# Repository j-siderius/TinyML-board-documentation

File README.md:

# TinyML Board Documentation

The TinyML board is a development board specifically tailored to the exploration of TinyML concepts and to test possible applications of TinyML in an easy way. It features a powerfull microcontroller as well as a suite of sensors to sense the environment. Combined with a special TensorFlow Lite Micro library, it is easy to use this devide and start deploying machine learning models to the Edge.

<div align="center">
    
</div>

## Contents
- [Quick start](#quick-start)
- [Hardware](#hardware)
  - [Sensors](#sensors)
  - [Processor](#processor)
  - [Input/Output](#inputoutput)
  - [Expansion headers](#expansion-headers)
- [Software](#software)
  - [Arduino](#arduino-ide)
  - [IDE configuration](#ide-configuration)
  - [Serial Port Setup](#serial-port-setup)
  - [Libraries](#arduino-libraries)
  - [TensorFlow Lite Micro library](#tensorflow-lite-micro-library)
  - [Uploading code](#uploading-code)
- [Code examples](#code-examples)
  - [Sensor examples](#sensor-examples)
  - [I/O examples](#io-examples)
  - [TensorFlow Lite Micro examples](#tensorflow-lite-micro-examples)
  - [Board tests](#board-tests)
- [Frequently Encountered Issues](#frequently-encountered-issues)
- [License](#license-and-contact)

## Quick start

 1. Install the ESP32 board support into Arduino IDE by adding the Espressif repository to the Board Manager and then downloading the ESP32 boards - [Espressif Arduino ESP32 installation](https://docs.espressif.com/projects/arduino-esp32/en/latest/installing.html#installing-using-arduino-ide).
 2. Install libraries for the sensors ([Sparkfun BME280](https://github.com/sparkfun/SparkFun_BME280_Arduino_Library), [Sparkfun BMI270](https://github.com/sparkfun/SparkFun_BMI270_Arduino_Library), [Pololu VL53L0X](https://github.com/pololu/vl53l0x-arduino) and [FastLED](https://github.com/FastLED/FastLED)) using the Library Manager and TensorFlow Lite Micro ([TFLiteMicro_ArduinoESP32S3](https://github.com/j-siderius/TFLiteMicro_ArduinoESP32S3)) from the GitHub page.
 3. Choose an [example project](#code-examples) for the TinyML board and load the code into Arduino IDE.
 4. Configure the TinyML board using the [Arduino IDE settings](#ide-configuration). Press and hold the `Upload/Btn1` button, then press the `RESET` button. Release all buttons and click `Upload`, then wait for the code to upload.
 5. Check the Serial Monitor or Serial Plotter in Arduino IDE to see the output from the model.

More detailed instructions can be found in the corresponding sections below.

[🔼 Back to the top](#tinyml-board-documentation)

## Hardware

The TinyML board contains several sensors and a powerfull processor to get up and running with TinyML quickly. In the following sections, a general overview as well as technical details on all hardware can be found.

<div align="center">
    
</div>

### Sensors

The TinyML board contains five different sensors that can be used for gathering data. To see how to use the sensors, look at the [Code Examples](#code-examples). For detailed information about the circuit board, refer to the [Circuit board documentation](/pcb/README.md).

- **Microphone (I2S)** [_ICS-43434_](assets/datasheets/ics43434.pdf) - This sensor measures the amplitude and pitch of sound.
- **Time-of-Flight range sensor** [_VL53L0X_](assets/datasheets/vl53l0x.pdf) - This sensor measures short-range distance.
- **Environmental sensor** [_BME280_](assets/datasheets/bme280.pdf) - This sensor measures temperature, relative humidity and atmospheric pressure.
- **Hall effect magnet sensor** [_AH49E_](assets/datasheets/ah49e.pdf) - This sensor measures the magnetic field around its axis.
- **Inertial Measurement Unit (IMU)** [_BMI270_](assets/datasheets/bmi270.pdf) - This sensor measures both the angular motion using a gyroscope, as well as the acceleration using an accelerometer.

### Processor

The TinyML board is fitted with an ESP32-S3 SoC. The processor features a fast 240MHz, dual-core processor, large 16MB storage and 8MB RAM. 
Additionally, it has Bluetooth 5 and WiFi capabilities, making it easy to connect the TinyML board to the internet, for example to share sensor data.
More information about the onboard chip can be found in the datasheet: [ESP-S3-WROOM1-N16R8](assets/datasheets/esp32s3wroom1.pdf).

### Input/Output

Besides sensors, the TinyML board also contains multiple Inputs and Outputs (I/O). To see how to use the I/O, look at the [Code Examples](#code-examples).

- **Buttons** - Two buttons are accessible to the user (`Upload/Btn1` and `Btn2`), which can be user-configured. Both buttons need to be pulled high by the processor (see the [Code Examples](#code-examples)).
  The last button (`RESET`) is used if the board needs to be programmed or debugged, e.g. if the TinyML board or the application need to be restarted.
- **Output LED** - The red LED can be used as simple output, e.g. for showing if a sensor functions properly. The output LED is marked `LED` on the TinyML board.
- **Neopixels** - The Neopixel LEDs can be addressed individually to display RGB colors. They can output application information, give users feedback and more. The Neopixels are marked `Neopixels` on the TinyML board.

- **USB-C connector** - This connector is primarily used for programming and serial communication with the TinyML board. It is also the primary power input for the board. To program the board, a USB-C _Data_ cable is needed.
- **Stemma QT / QWIIC** - This connector enables users to connect extra sensors, making the TinyML board suitable for even more advanced projects.
  The connector uses the popular [Adafruit Stemma QT](https://www.adafruit.com/category/620) and [SparkFun QWIIC](https://www.sparkfun.com/categories/399) standards, opening up the possibilty for many extra sensors.
  Using a Stemma QT expansion board, users can connect even more sensors in series. For the pinout, refer to the [Expansion headers](#expansion-headers) section. This connector if marked `Stemma QT/QWIIC` on the TinyML board.
- **Expansion header** - This connector can be used to connect extra peripherals, sensors, actuators and more to adapt the TinyML board to different projects. This connector is marked `Expansion Header` on the TinyML board.
  The connector features power, digital and analog connections, as well as support for the SPI high-speed databus. In combination with the ESP32S3's built in GPIO multiplexer, the connector gives the freedom to connect many different things to the TinyML board.
  For the pinout, refer to the [Expansion headers](#expansion-headers) section.

- **Miscellaneous** - The TinyML board also contains some other, miscellaneous component.
  These components are used to show power (green LED, marked `ON` on the TinyML board), convert voltage, debug the TinyML board (header, marked `Debugging` on the TinyML board) and some other passive components. Additionally, the board features some test-points (2x GND, VUSB, 3.3V and IO0) which can be used to verify the functionality of some components.

### Expansion headers

Below a systematic overview of all expansion headers present on the TinyML board is shown. The Expansion header features four analog GPIO pins (A1 - A4 in the top row), four digital GPIO pins (D1 - D4 in the bottom row), as well as 3.3V power and ground (GND). The digital GPIO pins also expose the SPI data bus of the ESP32S3 microcontroller as follows:

| GPIO pin | Description |
| --- | --- |
| D1 / GPIO14 | SPI CS |
| D2 / GPIO11 | SPI MOSI |
| D3 / GPIO12 | SPI SCK |
| D4 / GPIO13 | SPI MISO |

The TinyML board can technically be powered through the Expansion Header, but the power should be stable and noise-free **3.3V** only. If the external power is fluctuating, the microcontroller could be damaged. If it is absolutely nescessary to provide variable external power from another source than USB-C (e.g. from a battery), it is possible to utilise the testpoints GND and VUSB close to the USB-C connector on the board. The VUSB testpoint routes the power through the on-board voltage regulator first, which produces clean 3.3V.

<div align="center">
    
</div></div>

[🔼 Back to the top](#tinyml-board-documentation)

## Software

In order to use the TinyML board, it needs to be correctly setup. The TinyML board requires no hardware setup, but it does require some software setup. In order to start using it, connect a USB-C _Data_ cable to the board and plug it into a free USB port on the system. Below sections detail the setup of the Arduino IDE, installation of sensor libraries and finally the TensorFlow Lite Micro setup.

### Arduino IDE

The TinyML board can be programmed using the [Arduino IDE](https://www.arduino.cc/en/software), both the new 2.x and Legacy >1.8 versions.
Please make sure that the Arduino IDE is installed on the system before continuing.

In order to program the TinyML board, the [ESP32](#processor) platform need to be installed. To do this, follow the steps below:

1. Open the Arduino IDE and navigate to the `Preferences` (_Windows_: File > Preferences, _Mac_: Arduino > Preferences), as shown in the left image below.
2. In the field `Additional boards manager URLs:` enter the following link (If there are already other URLs in this field,
   open the full list by clicking the folder icon to the right of the URL):
   ```
   https://espressif.github.io/arduino-esp32/package_esp32_index.json
   ```   
3. Press `Ok` to close the `Preferences`.
4. Open the `Boards Manager` by going to Tools > Boards > Boards Manager.
5. Search for **ESP32** and install the platform by Espressif Systems.
6. Restart the Arduino IDE.

<div align="center">

</div>

For more advanced installations, for example in Platform IO, follow this [advanced installation guide](https://docs.espressif.com/projects/arduino-esp32/en/latest/installing.html).

### IDE configuration

In order to use all functions that the ESP32S3 processor has, Arduino IDE must be properly configured when programming the TinyML board. Below are the most important settings, these need to be configured in the `Tools menu` (_Windows_ + _Mac_: Tools) by clicking on the setting and choosing the correct option:

- **Board** - *ESP32S3 Dev Module*: This sets the correct processor and board configuration for the TinyML board. To select the ESP32 Dev Module, first select the *esp* platform.
- **Port** - *port here*: Enter the serial port of the TinyML board here. Refer to the guide [Serial Port](#serial-port-setup) to find this port.
- **USB CDC On Boot** - *Enabled*: This setting enables the onboard USB-C port to be used for serial communication.
- **Flash mode** - *DIO 80MHz*: This setting configures the correct mode for writing to the flash of the ESP32S3.
- **Flash Size** - *16MB (128Mb)*: This setting uses the full storage of the ESP32S3, enabling space for larger projects and more code.
- **PSRAM** - *OPI PSRAM*: This setting enables the fast built-in RAM of the ESP32S3.

<div align="center">
    
</div>

### Serial Port setup

No drivers are required for the TinyML board. However, sometimes, it is nescessary to know on which serial port the TinyML board is connected. To find this out, perform the following steps:

_Arduino IDE_
1. Open the `Port overview menu` (_Windows_ + _Mac_: Tools > Port) and observe which ports are in the list. 
2. Close the list.
3. Plug in the TinyML board and open the `Port overview menu`, observe which port was added to the list > this is the TinyML board port.

If the above method does not work, an OS-specific check can be done using the instructions below:

_Windows_
1. Open `Device Manager` by going to Start and searching for the program. (Alternatively, press the <kbd></kbd> key and search for Device Manager)
2. Open the `Ports (COM & LPT)` section.
3. Plug in the TinyML board and observe which COM port was added to this list > this is the TinyML board port.

_Mac_
1. Open the `Terminal` application by going to Applications > Utilities. (Alternatively, press the <kbd> + Spacebar</kbd> keys and search for Terminal)
2. Enter the following command `ls /dev/tty*` and press <kbd>Enter</kbd>.
3. Plug in the TinyML board and repeat step 2, observe which port was added to the list > this is the TinyML board port.

### Arduino libraries

In order to use the sensors on the TinyML board, some Arduino libraries are needed. The recommended libraries are listed below, although other libraries might work as well.

The libraries can be installed into Arduino IDE through the Library Manager (Sketch > Include Library > Manage Libraries). The versions are included here for documentation purpose, the newest version of each library should work fine.

- [Sparkfun BME280](https://github.com/sparkfun/SparkFun_BME280_Arduino_Library) (2.0.10 or later)
- [SparkFun BMI270](https://github.com/sparkfun/SparkFun_BMI270_Arduino_Library) (1.0.3 or later)
- [Pololu VL53L0X](https://github.com/pololu/vl53l0x-arduino) (1.3.1 or later)
- [FastLED](https://github.com/FastLED/FastLED) (3.9.13 or later)

The onboard [Microphone](#sensors) uses the built-in I2S library from Espressif, so there is no library to install to use the microphone. More information can be found in the [I2S Peripherals documentation](https://docs.espressif.com/projects/esp-idf/en/v3.3/api-reference/peripherals/i2s.html). 

### TensorFlow Lite Micro library

In order to run TensorFlow Lite Micro models on the TinyML board, the [TFLiteMicro_ArduinoESP32S3](https://github.com/j-siderius/TFLiteMicro_ArduinoESP32S3) library needs to be installed. Download the libary from its homepage and install it in the Arduino IDE by using the Library Manager (Sketch > Include Library > Add .ZIP Library). More information on installing ZIP-libraries on Arduino can be found on the [Arduino website](https://docs.arduino.cc/software/ide-v1/tutorials/installing-libraries/#importing-a-zip-library).

> [!IMPORTANT]
> Be aware that not all TensorFlow (Keras) layers are supported by TensorFlow Lite Micro. Some layers may also have a different name in TensorFlow Lite Micro, compared to their name in TensorFlow (Keras), for example the `LSTM` layer is called `UnidirectionalSequenceLSTM`.
> 
> <details><summary>Supported layers</summary>
> Abs
> Add
> AddN
> ArgMax
> ArgMin
> AssignVariable
> AveragePool2D
> BatchMatMul
> BatchToSpaceNd
> BroadcastArgs
> BroadcastTo
> CallOnce
> Cast
> Ceil
> CircularBuffer
> Concatenation
> Conv2D
> Cos
> CumSum
> Delay
> DepthToSpace
> DepthwiseConv2D
> Dequantize
> DetectionPostprocess
> Div
> EmbeddingLookup
> Energy
> Elu
> Equal
> EthosU
> Exp
> ExpandDims
> FftAutoScale
> Fill
> FilterBank
> FilterBankLog
> FilterBankSquareRoot
> FilterBankSpectralSubtraction
> Floor
> FloorDiv
> FloorMod
> Framer
> FullyConnected
> Gather
> GatherNd
> Greater
> GreaterEqual
> HardSwish
> If
> Irfft
> L2Normalization
> L2Pool2D
> LeakyRelu
> Less
> LessEqual
> Log
> LogicalAnd
> LogicalNot
> LogicalOr
> Logistic
> LogSoftmax
> Maximum
> MaxPool2D
> MirrorPad
> Mean
> Minimum
> Mul
> Neg
> NotEqual
> OverlapAdd
> Pack
> Pad
> PadV2
> PCAN
> Prelu
> Quantize
> ReadVariable
> ReduceMax
> Relu
> Relu6
> Reshape
> ResizeBilinear
> ResizeNearestNeighbor
> Rfft
> Round
> Rsqrt
> SelectV2
> Shape
> Sin
> Slice
> Softmax
> SpaceToBatchNd
> SpaceToDepth
> Split
> SplitV
> Squeeze
> Sqrt
> Square
> SquaredDifference
> StridedSlice
> Stacker
> Sub
> Sum
> Svdf
> Tanh
> TransposeConv
> Transpose
> Unpack
> UnidirectionalSequenceLSTM
> VarHandle
> While
> Window
> ZerosLike
> </details>

<!-- Not all normal TensorFlow Ops (layers) are supported by TensorFlow Lite Micro. In order to see what operations the TensorFlow model uses, you can upload your saved model to [Netron](https://netron.app/) and examine it. The supported operations in this version of TensorFlow Lite Micro can be found in the [Arduino-TensorFlowLite-ESP32 README](/arduino-tensorflowlite-esp32/README.md#supported-ops). -->

<!-- > [!IMPORTANT]
> The TensorFlow Lite Micro ESP32 library included in this repository works with the TensorFlow Lite Micro release from Feb 2023.
> With much manual modifications, the library can be updated, however there is no compatibility guarantee as much of the TensorFlow Lite Micro codebase has changed without proper notice and documentation. -->

### Uploading code

To upload a program to the TinyML board, follow the steps below:

1. Connect the TinyML board to the system using a USB-C _Data_ cable.
2. Ensure that the IDE settings are setup as described in the [Arduino IDE](#arduino-ide) and [IDE configuration](#ide-configuration) sections.
3. Select the correct serial port for the TinyML board, as described in the [Serial Port setup](#serial-port-setup) section.
4. Optionally, on older versions of the Arduino IDE: Press and hold the `Upload/Btn1` button, then press the `RESET` button. This puts the ESP32S3 into *Upload*\* mode. Release all buttons after a couple of seconds.
5. Click `Upload`, then wait for the code to upload.

\* Technically, this mode is called *Download*, since the code is downloaded to the microcontroller, but for ambiguities sake, it is called *Upload* here.

[🔼 Back to the top](#tinyml-board-documentation)

## Code examples

Example code for all described functions of the TinyML board can be found below. They are divided into sensors, I/O and TensorFlow Lite Micro examples.

The TinyML board usually comes pre-programmed with a Board Test firmware. This program tests all functionality of the TinyML board. To start the test, just connect the TinyML board to the system and open the Serial Monitor in Arduino IDE (_Windows_ + _Mac_: either through GUI button or Tools > Serial Monitor).

Additional (advanced) examples can be found in the [ESP32 Arduino library documentation](https://docs.espressif.com/projects/arduino-esp32/en/latest/libraries.html).

### Sensor examples

<!---
- Microphone 
--->
- Microphone => Currently there is a software bug that prevents the microphone from being used
- Time-of-Flight sensor 
- Environmental sensor 
- Hall-effect magnetic sensor 
- Inertial Measurement Unit (IMU) 

### I/O examples

- Buttons 
- LED 
- Neopixels 
- Expansion header 

### TensorFlow Lite Micro examples

Please find all TensorFlow Lite Micro examples in the TFLiteMicro_ArduinoESP32S3 library repository: [TFLiteMicro_ArduinoESP32S3 examples](https://github.com/j-siderius/TFLiteMicro_ArduinoESP32S3/#examples).

### Board tests

- TinyML Board Test 

[🔼 Back to the top](#tinyml-board-documentation)

## Frequently Encountered Issues

#### The TinyML board serial port does not appear in Arduino IDE when connected

Make sure to use a USC-C _Data_ cable, since the TinyML board can only communicate with the system when it has both power and data connections. Some cheaper cables only provide power wires.

#### The ESP32S3 Dev Module cannot be selected as board in Arduino IDE

Make sure to have the ESP32 platform installed in the Arduino IDE. Refer to the [Software - Arduino IDE](#arduino-ide) section for a guide how to do this.

#### It is not possible to upload code to the TinyML board

When getting a `Failed to connect to ESP32-S3` error in Arduino IDE, it is possible that the TinyML board was not in Upload mode. To get the TinyML board in this mode, follow the [Uploading code](#uploading-code) section. 
<!-- Alternatively, update the Arduino IDE to the latest version (2.3.4 as of February 2025) and update the ESP32 platform to the latest version (3.1.1 as of February 2025); the upload process will now be automated. -->

#### The serial upload fails

When getting an `A serial exception error occurred` error in Arduino IDE, there are multiple possibilities:
- If the writing and verification of bytes was successful, check if the Arduino code works as expected, usually the code was uploaded correctly, but the programmer fails after the restart.
- If the writing was not successful, follow the troubleshooting steps on the [Espressif Esptool website](https://docs.espressif.com/projects/esptool/en/latest/esp32/troubleshooting.html).

#### Missing library in Arduino IDE

When getting an `Fatal error: <library_name>.h: No such file or directory` error in Arduino IDE, it is likely that the software library required for the code is not installed. Follow the [Arduino libraries](#arduino-libraries) section to install all required libraries.

#### Arduino sketch too large

When getting an `Sketch too big` error, the storage of the TinyML board was exceeded. First, make sure that Arduino utilises the whole onboard Flash memory by checking the [IDE configuration](#ide-configuration). If the code is still too large, decrease the Arduino sketch size:
- Reduce the size of bytearrays included in the code (e.g. storing images).
- Reduce the size of the TensorFlow Lite Micro model by tweaking the TensorFlow model (e.g. by condensing or removing layers).
- Reduce the amount of libraries that are included in the Arduino sketch, especially if they are unused.

#### Code contains unsupported operators

When getting an `Encountered ERROR: TFLite operator with code <code_here> is unsupported` error, an operator or layer that is not supported by TFLite Micro was present in the code. When making the TensorFlow model that will be utilised on the TinyML board, make sure to only use the supported layers. These are described in the [TensorFlow Lite Micro library](#tensorflow-lite-micro-library) section.

#### The TinyML board does not print any output to the Serial Monitor

If no output is found on the Serial Monitor in Arduino IDE, the USB CDC option is probably misconfigured. Refer to the [IDE configuration](#ide-configuration) section to setup the *USB CDC on Boot* option correctly.

If the Serial Monitor in Arduino IDE only displays garbage output, make sure that the correct baudrate is set up. The default baudrate for the [Code examples](#code-examples) is `115200`. Refer to the [Arduino Serial Monitor](https://docs.arduino.cc/software/ide-v2/tutorials/ide-v2-serial-monitor/#using-the-serial-monitor-tool) guide to configure the Serial Monitor.

#### TinyML board keeps crashing after uploading code

When getting a looping error `rst:0x10  (RTCWDT_RTC_RESET),boot:0x13 (SPI_FAST_FLASH_BOOT)`, `rst:0x3 (SW_RESET),boot:0x13 (SPI_FAST_FLASH_BOOT)` or `rst:0x1  (POWON),boot:0xd (SPI_FAST_FLASH_BOOT)`, this means that the TinyML board is stuck in a boot loop. Usually this problem is caused by a fault, overload or memory corruption problem in the code, so check the whole Arduino code for errors.

#### Onboard sensors are not initialising or giving error

Make sure to use the correct I2C addresses for all of the onboard sensors. The [Sensor code examples](#sensor-examples) for each sensor contain the correct I2C address and initialisation code. The addresses are also listed below:

- **BMI270** - `0x69`
- **BME280** - `0x76`
- **VL53L0X** - `0x29`

#### Onboard buttons do not recognised presses

Make sure to pullup both onboard buttons (`Upload/Btn1` and `Btn2`), like shown in the [I/O code examples](#io-examples). Both buttons should be initialised using the `INPUT_PULLUP` option in Arduino. An example code for a button could be:

```cpp
#define pin_button1 0
void setup() {
  pinMode(pin_button1, INPUT_PULLUP);
}
```

#### TinyML board crashed randomly on brownout

When getting a `Brownout detector was triggered` error message, the TinyML board temporarily received too little power to run the microcontroller (called a brownout). The brownout occurs when the microcontroller and pheripherals draw much power, for example during sensor readings or large calculations. This problem is usually caused by either a bad USB-C _Data_ cable (with thin wires) or a bad power supply (e.g. the computer USB port not providing enough current). To solve this, try another USB-C _Data_ cable and / or power supply.

[🔼 Back to the top](#tinyml-board-documentation)

## License

$\color{red}{\textsf{TODO:}}$ Add license information here

<br>

[🔼 Back to the top](#tinyml-board-documentation)

&copy; Jannick Siderius

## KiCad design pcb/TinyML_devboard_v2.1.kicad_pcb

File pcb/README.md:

# Circuit Board documentation

This folder contains the circuit board files and schematics.

The PCB was setup and designed in [KiCad 7](https://www.kicad.org/).

Boards were manufactured and assembled by [Eurocircuits](https://www.eurocircuits.com/) in Belgium.

## Pin layout

The pin layout of the ESP32S3 is as follows:

| Pin | Connection |
|---|---|
| IO0 | Button 1 / Upload |
| IO1 | Analog 1 |
| IO2 | Analog 2 |
| IO3 | Analog 3 |
| IO4 | Analog 4 |
| IO5 | I2S SD |
| IO6 | I2S WS |
| IO7 | I2S SCK|
| IO8 | I2C SDA |
| IO9 | I2C SCL |
| IO10 | Hall Effect sensor |
| IO11 | SPI MOSI / Digital 2 |
| IO12 | SPI SCK / Digital 3 |
| IO13 | SPI MISO / Digital 4 |
| IO14 | SPI CS / Digital 1 |
| IO17 | LED |
| IO18 | Neopixels |
| IO19 | USB D- |
| IO20 | USB D+ |
| IO21 | IMU wake interrupt |
| IO47 | Button 2 |
| TXD0 | TX |
| RXD0 | RX |

## I2C addresses

The sensors are connected with the following I2C addresses:

- **BMI270** - 0x69
- **BME280** - 0x76
- **VL53L0X** - 0x29

<br>

&copy; Jannick Siderius

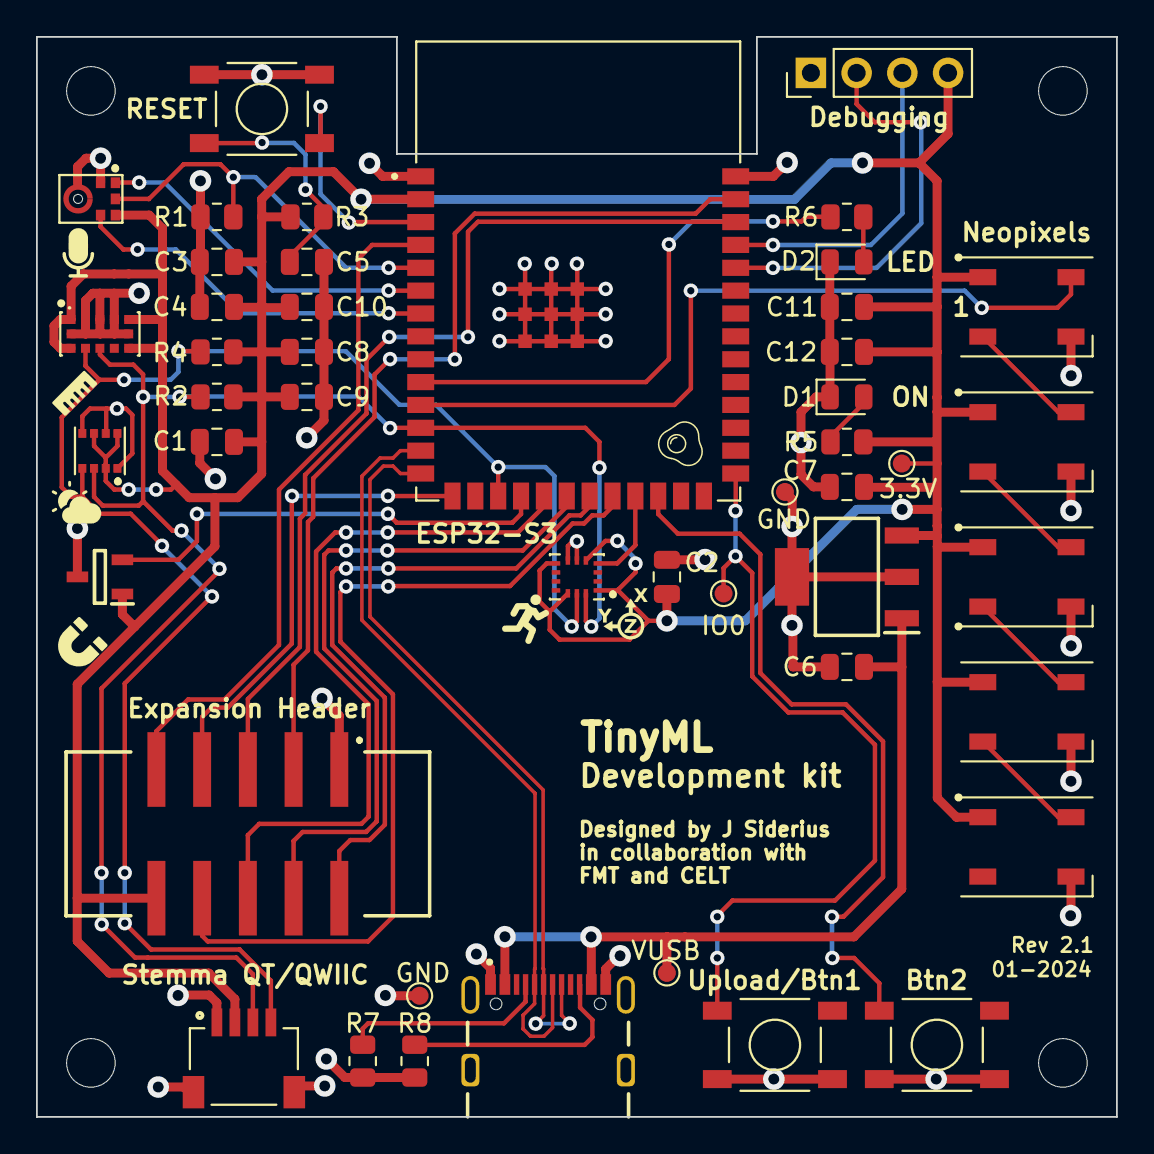
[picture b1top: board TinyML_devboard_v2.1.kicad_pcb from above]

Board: 2 copper layers, 60.0 x 60.0 mm, 50 parts (0 on the bottom side), 36 nets.

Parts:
3.3V: TestPoint; TestPoint_Pad_D1.0mm
C1, C2, C3, C4, C11: 0.1u; C_0805_2012Metric
C5: 1u; C_0805_2012Metric
C6, C7: 4.7u; C_0805_2012Metric
C8, C9, C10, C12: 10u; C_0805_2012Metric
D1: LED_G; LED_0805_2012Metric
D2: LED_R; LED_0805_2012Metric
D3, D4, D5, D6, D8: WS2812B; LED_WS2812B_PLCC4_5.0x5.0mm_P3.2mm
GND: TestPoint; TestPoint_Pad_D1.0mm
GND#2: TestPoint; TestPoint_Pad_D1.0mm
H1, H2, H3, H4: MountingHole; MountingHole_2.7mm_M2.5
IC1: AH49ENTR-G1; SOT95P280X145-3N
IO0: TestPoint; TestPoint_Pad_D1.0mm
J1: Conn_01x04; PinHeader_1x04_P2.54mm_Vertical
J2: SM04B-SRSS-TB_LF__SN_; JST_SM04B-SRSS-TB_LF__SN_
J3: SBH11-NBPC-D05-SM-BK; SBH11NBPCD05SMBK
J4: USB4105GFA; GCT_USB4105GFA
MK1: ICS-43434; MIC_ICS-43434
PS1: AP2114HA-3.3TRG1; SOT230P700X180-4N
R1: 100k; R_0805_2012Metric
R2, R3, R4: 10k; R_0805_2012Metric
R5, R6: 1k; R_0805_2012Metric
R7, R8: 5.1k; R_0805_2012Metric
S1, S2, S3: PTS525SM15SMTR2LFS; SW_PTS525SM15SMTR2LFS
U1: BME280; PSON65P250X250X100-8N
U2: BMI270; XDCR_BMI270
U3: VL53L0CXV0DH_1; XDCR_VL53L0CXV0DH_1
U4: ESP32-S3-WROOM-1-N16R8; XCVR_ESP32-S3-WROOM-1-N16R8
VUSB: TestPoint; TestPoint_Pad_D1.0mm

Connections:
+3.3V: 3.3V.1, C1.1, C2.1, C3.1, C4.1, C7.1, C8.1, C9.1, C10.1, C11.1, C12.1, D3.1 (VDD), D4.1 (VDD), D5.1 (VDD), D6.1 (VDD), D8.1 (VDD), IC1.1 (VCC), J1.4, J2.2, J3.10, MK1.5 (VDD), PS1.3 (VOUT), R2.1, R3.1, R4.1, R5.2, U1.2 (CSB), U1.6 (VDDIO), U1.8 (VDD), U2.1 (SDO), U2.5 (VDDIO), U2.8 (VDD), U2.12 (CSB), U3.1 (AVDDVCSEL), U3.1.1 (AVDDVCSEL), U3.5 (XSHUT), U3.7 (GPIO1), U3.11 (AVDD), U4.2 (3V3)
ANALOG_1: J3.3, U4.39 (IO1)
ANALOG_2: J3.5, U4.38 (IO2)
ANALOG_3: J3.7, U4.15 (IO3)
ANALOG_4: J3.9, U4.4 (IO4)
BOOT/BTN1: IO0.1, S1.1, U4.27 (IO0)
BTN2: S2.1, U4.24 (IO47)
CC1: J4.A5 (CC1), R7.1
CC2: J4.B5 (CC2), R8.1
GND: C1.2, C2.2, C3.2, C4.2, C5.2, C6.2, C7.2, C8.2, C9.2, C10.2, C11.2, C12.2, D1.1 (K), D2.1 (K), D3.3 (VSS), D4.3 (VSS), D5.3 (VSS), D6.3 (VSS), D8.3 (VSS), GND.1, GND#2.1, IC1.3 (GND), J1.1, J2.1, J2.S1 (SHIELD), J2.S2 (SHIELD), J3.1, J4.A1_B12 (GND), J4.B1_A12 (GND), J4.SH1 (SHELL_GND), J4.SH2 (SHELL_GND), J4.SH3 (SHELL_GND), J4.SH4 (SHELL_GND), MK1.2 (LR), MK1.3 (GND), PS1.2 (GND_1), PS1.4 (GND_2), R1.2, R7.2, R8.2, S1.3, S1.4, S2.3, S2.4, S3.3, S3.4, U1.1 (GND), U1.5 (SDO), U1.7 (GND), U2.6 (GNDIO), U2.7 (GND), U3.2 (AVSSVCSEL), U3.3 (GND), U3.4 (GND), U3.6 (GND), U3.12 (GND), U4.1 (GND), U4.40 (GND), U4.41_7 (GND)
HALL_SENS: IC1.2 (OUT), U4.18 (IO10)
I2S_SCK: MK1.4 (SCK), U4.7 (IO7)
I2S_SD: MK1.6 (SD), R1.1, U4.5 (IO5)
I2S_WS: MK1.1 (WS), U4.6 (IO6)
IMU_WAKE: U2.4 (INT1), U4.23 (IO21)
LED: R6.2, U4.10 (IO17)
NEOPIX: D3.4 (DIN), U4.11 (IO18)
unnamed: C5.1, R3.2, S3.2
unnamed: D1.2 (A), R5.1
unnamed: D2.2 (A), R6.1
unnamed: D3.2 (DOUT), D4.4 (DIN)
unnamed: D4.2 (DOUT), D5.4 (DIN)
unnamed: D5.2 (DOUT), D6.4 (DIN)
unnamed: D6.2 (DOUT), D8.4 (DIN)
RESET: S3.1, U4.3 (EN)
SCL: J2.4, R4.2, U1.4 (SCK), U2.13 (SCX), U3.10 (SCL), U4.17 (IO9)
SDA: J2.3, R2.2, U1.3 (SDI), U2.14 (SDX), U3.9 (SDA), U4.12 (IO8)
SPI_CS: J3.8, U4.22 (IO14)
SPI_MISO: J3.2, U4.21 (IO13)
SPI_MOSI: J3.6, U4.19 (IO11)
SPI_SCK: J3.4, U4.20 (IO12)
UART_RX: J1.2, U4.36 (RXD0)
UART_TX: J1.3, U4.37 (TXD0)
USB_D+: J4.A6 (DP1), J4.B6 (DP2), U4.14 (IO20)
USB_D-: J4.A7 (DN1), J4.B7 (DN2), U4.13 (IO19)
VDD: C6.1, J4.A4_B9 (VBUS), J4.B4_A9 (VBUS), PS1.1 (VIN), VUSB.1

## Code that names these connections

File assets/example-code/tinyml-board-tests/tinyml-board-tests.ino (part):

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#define pin_analog2 2
#define pin_analog3 3
#define pin_analog4 4
#define pin_i2s_sd 5
#define pin_i2s_ws 6
#define pin_i2s_sck 7
#define pin_i2c_sda 8
#define pin_i2c_scl 9
#define pin_hall_eff 10
#define pin_spi_mosi 11
#define pin_spi_sck 12
#define pin_spi_miso 13
#define pin_spi_cs 14
#define pin_led 17
#define pin_neopixel 18
#define pin_imu_wake 21
#define pin_button2 47

BME280 envSensor;
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//   .fixed_mclk = 0
// };
// i2s_pin_config_t i2s_mic_pins = {
//   .bck_io_num = pin_i2s_sck,
//   .ws_io_num = pin_i2s_ws,
//   .data_out_num = I2S_PIN_NO_CHANGE,
//   .data_in_num = pin_i2s_sd
// };

void setup() {
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
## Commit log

2024-03-24 Created README.md
2024-03-24 Added initial assets (datasheets and images)
2024-03-24 Added initial images and datasheets to README
2024-03-24 Added version tracker to README
2024-03-24 Added images, changed content order, fixed image alignment
2024-03-24 Add download buttons, installation instruction images
2024-03-24 Added example code, Updated README
2024-03-24 Updated filepaths, Added README to TensorFLowLite library
2024-03-24 Added pcb information, updated README with uploading info
2024-03-24 fixed typo in pcb README
2024-03-24 Added board test code, updated README to include tests
2024-03-24 Updated supported ops in READMEs
2024-03-24 Updated Supported Ops
2024-03-25 Added schematic annotated board images to README
2024-03-25 Updated layout of README
2024-03-25 Updated upload instructions in README
2024-03-25 removed ambiguous statement on Downloading in README
2024-03-26 Updated supported Ops list
2024-03-26 Fixed button GPIO pin
2024-03-27 changed default baudrate in imu_example
2024-04-10 added extended flash instructions
2024-04-13 Added TFLM LSTM example + README changes
2024-04-13 Updated description of LSTM REadme
2024-04-13 Updated LSTM Readme, added background
2024-04-13 Added LSTM example notebook
2024-04-15 Added schematic, updated PCB file
2025-02-12 Updated README descriptions, clarified texts, added quick-start, modified markup, expanded expansion header section, modified images, added TODOs
2025-02-12 Rewrote TFLiteMicro library section, added available TFLM ops, linked TFLM examples
2025-02-12 Adapted all example code to new libraries and baudrate, changed README examples, removed TFLM examples (refer to library)
2025-02-12 Updated pcb README, added issues section to README
2025-02-13 Added troubleshooting steps to README
2025-03-27 Updated Quick Start to include Arduino settings
2026-03-24 Extended uploading description
2026-03-26 Update tinyml-board-tests.ino to relieve microphone test failing
2026-03-26 Update README.md with microphone information

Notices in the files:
README.md:
$\color{red}{\textsf{TODO:}}$ Add license information here
